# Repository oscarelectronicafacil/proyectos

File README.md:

Este repositorio es para almacenar todos los archivos necesarios para generar los prototipos, los proyectos realizados en las paginas webs OscarElectronicaFacil y hazloconarduino.

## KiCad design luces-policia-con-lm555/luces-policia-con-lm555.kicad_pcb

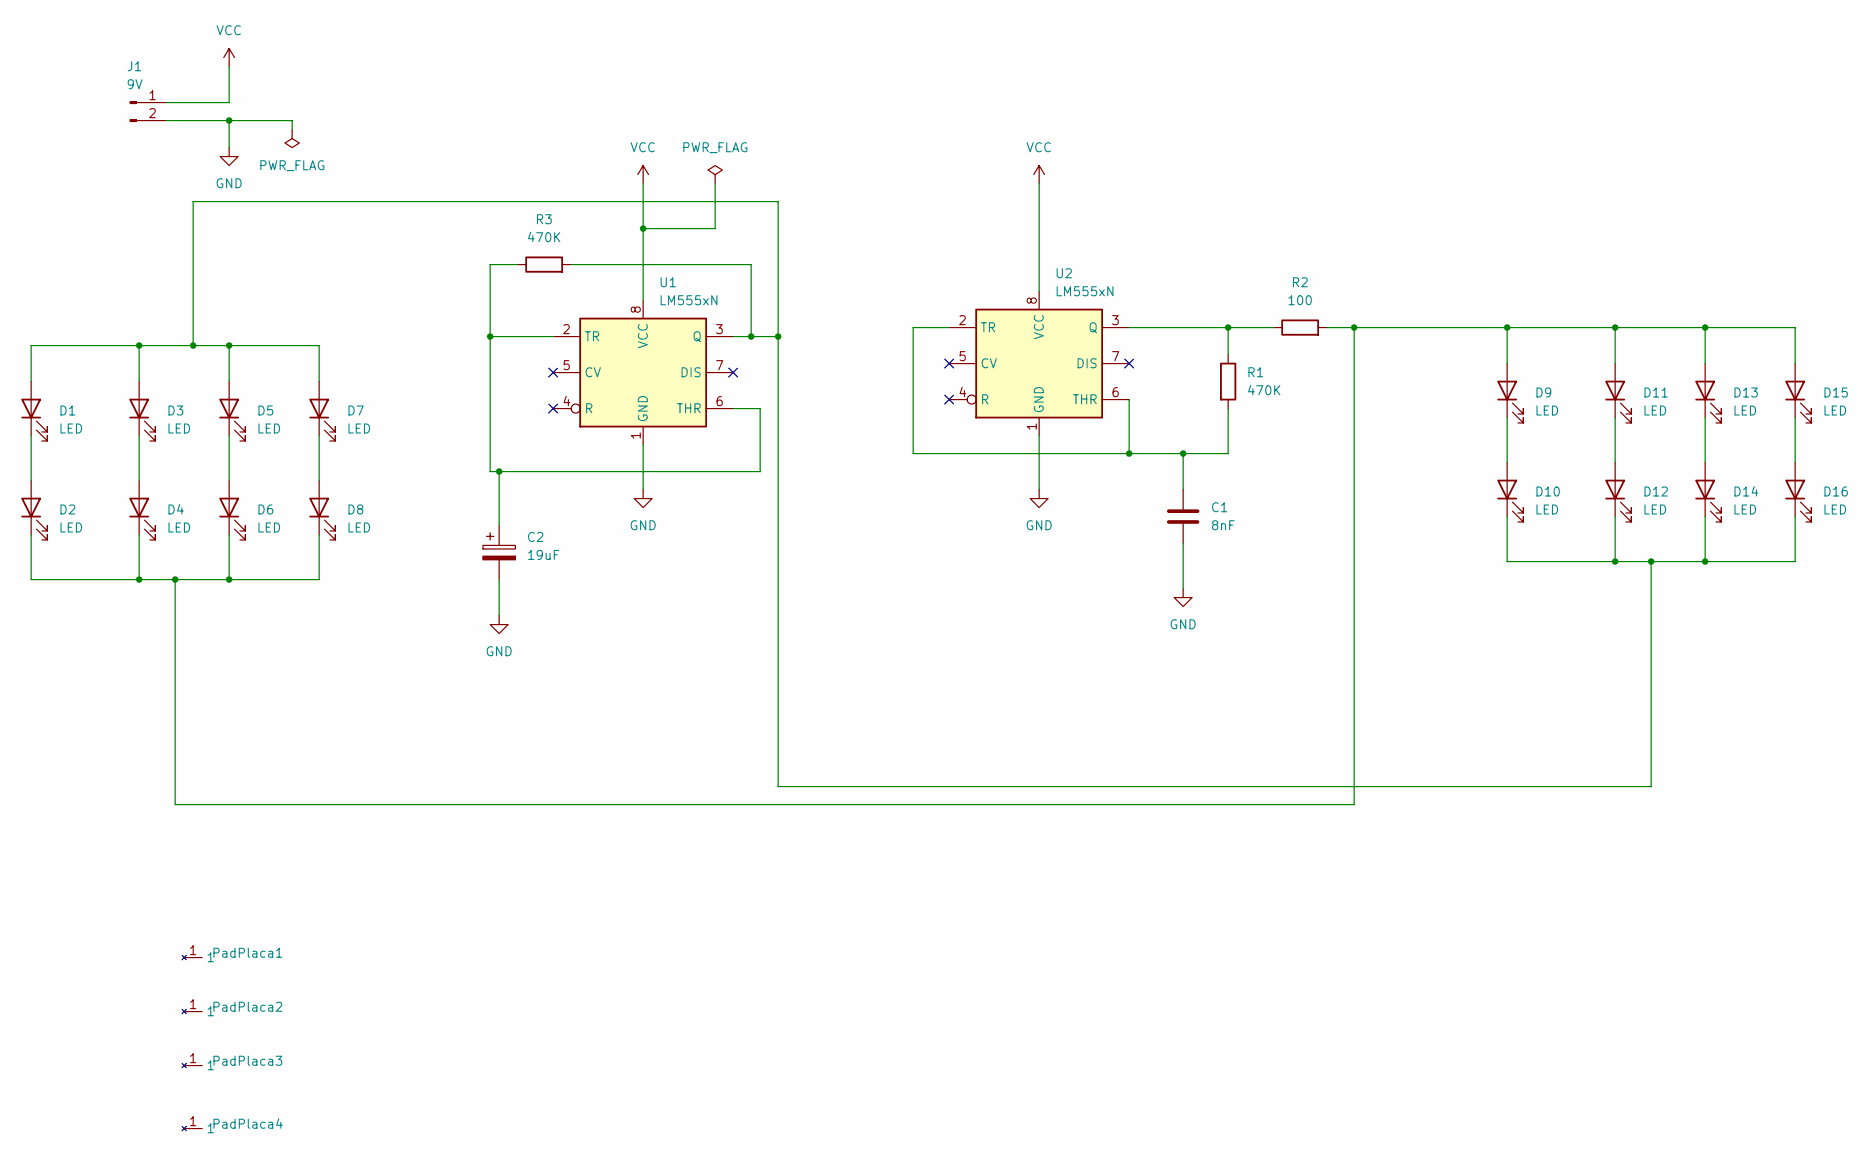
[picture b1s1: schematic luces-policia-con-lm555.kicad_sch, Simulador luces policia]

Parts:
C1: 8nF; C_Axial_L3.8mm_D2.6mm_P7.50mm_Horizontal
C2: 19uF; CP_Radial_D5.0mm_P2.50mm
D1, D2, D3, D4, D5, D6, D7, D8, D9, D10, D11, D12, D13, D14, D15, D16: LED; LED_D5.0mm
J1: 9V; PhoenixContact_MKDS_1,5_2-1727010-1x02_P3.50mm
PadPlaca1, PadPlaca2, PadPlaca3, PadPlaca4: pad
R1, R3: 470K; R_Axial_DIN0207_L6.3mm_D2.5mm_P10.16mm_Horizontal
R2: 100; R_Axial_DIN0207_L6.3mm_D2.5mm_P10.16mm_Horizontal
U1, U2: LM555xN; DIP-8_W7.62mm

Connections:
GND: C1.2, C2.2, J1.2, U1.1 (GND), U2.1 (GND)
unnamed: D1.2 (A), D3.2 (A), D5.2 (A), D7.2 (A), D10.1 (K), D12.1 (K), D14.1 (K), D16.1 (K), R3.2, U1.3 (Q)
unnamed: D1.1 (K), D2.2 (A)
unnamed: D3.1 (K), D4.2 (A)
unnamed: D5.1 (K), D6.2 (A)
unnamed: D7.1 (K), D8.2 (A)
unnamed: D9.1 (K), D10.2 (A)
unnamed: D2.1 (K), D4.1 (K), D6.1 (K), D8.1 (K), D9.2 (A), D11.2 (A), D13.2 (A), D15.2 (A), R2.2
unnamed: D11.1 (K), D12.2 (A)
unnamed: D13.1 (K), D14.2 (A)
unnamed: D15.1 (K), D16.2 (A)
unnamed: C2.1, R3.1, U1.2 (TR), U1.6 (THR)
unnamed: R1.1, R2.1, U2.3 (Q)
unnamed: C1.1, R1.2, U2.2 (TR), U2.6 (THR)
VCC: J1.1, U1.8 (VCC), U2.8 (VCC)

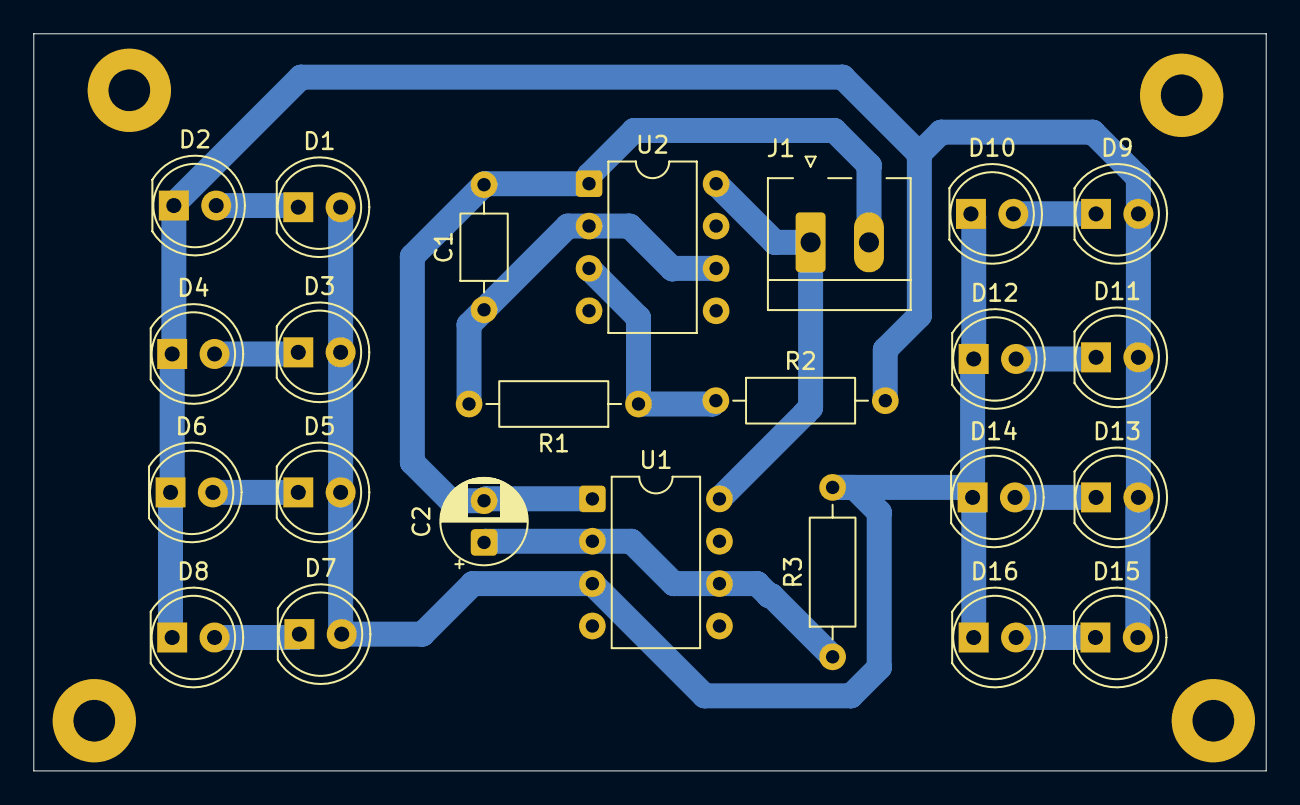
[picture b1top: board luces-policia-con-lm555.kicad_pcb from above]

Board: 2 copper layers, 73.9 x 44.2 mm, 28 parts (0 on the bottom side), 15 nets.

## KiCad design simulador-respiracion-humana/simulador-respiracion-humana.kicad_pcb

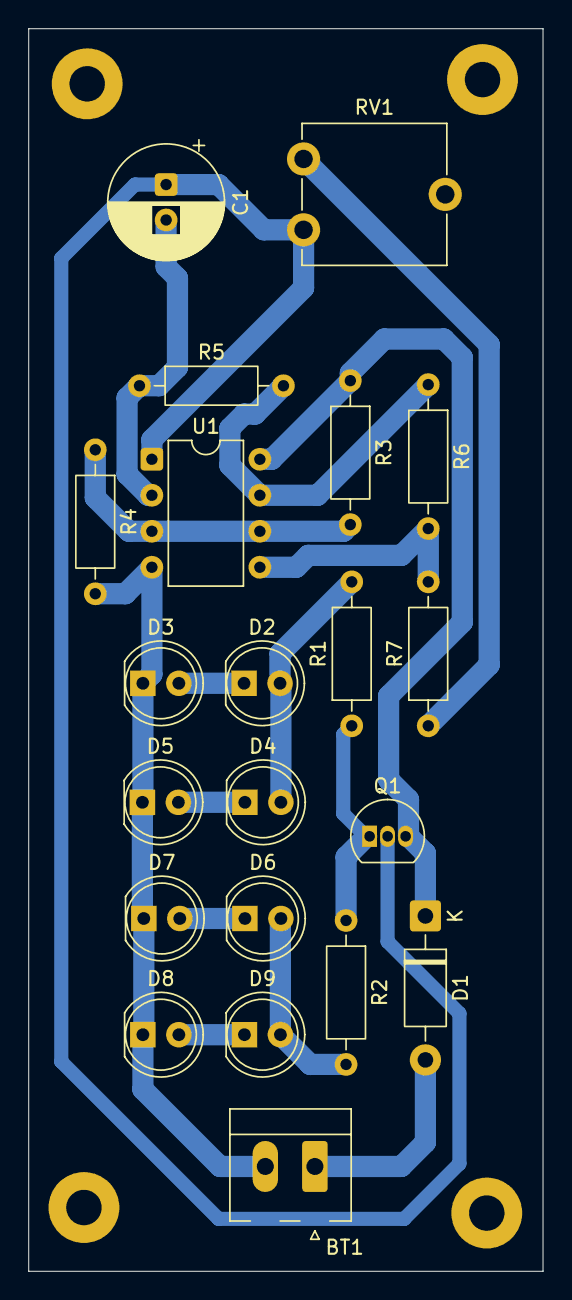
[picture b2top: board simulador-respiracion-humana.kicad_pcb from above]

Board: 2 copper layers, 36.3 x 87.7 mm, 25 parts (0 on the bottom side), 16 nets.

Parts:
BT1: 9V; PhoenixContact_MKDS_1,5_2-1727010-1x02_P3.50mm
C1: 22uF; CP_Radial_D8.0mm_P2.50mm
D1: 1N4007; D_DO-41_SOD81_P10.16mm_Horizontal
D2, D3, D4, D5, D6, D7, D8, D9: LED; LED_D5.0mm
PadPlaca1, PadPlaca2, PadPlaca3, PadPlaca4: pad
Q1: S8050; TO-92_Inline
R1, R2: 100; R_Axial_DIN0207_L6.3mm_D2.5mm_P10.16mm_Horizontal
R3, R4, R5: 47K; R_Axial_DIN0207_L6.3mm_D2.5mm_P10.16mm_Horizontal
R6: 100K; R_Axial_DIN0207_L6.3mm_D2.5mm_P10.16mm_Horizontal
R7: 33K; R_Axial_DIN0207_L6.3mm_D2.5mm_P10.16mm_Horizontal
RV1: 100K; Potentiometer_ACP_CA9-V10_Vertical
U1: DIP-8_W7.62mm

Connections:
unnamed: BT1.1 (+), D1.2 (A)
unnamed: BT1.2 (-), D3.1 (K), D5.1 (K), D7.1 (K), D8.1 (K), R4.2, U1.4
unnamed: C1.2, R5.1, U1.2
unnamed: D1.1 (K), Q1.3 (C), R3.1, U1.8
unnamed: D2.2 (A), D4.2 (A), R1.2
unnamed: D2.1 (K), D3.2 (A)
unnamed: D4.1 (K), D5.2 (A)
unnamed: D6.2 (A), D9.2 (A), R2.2
unnamed: D6.1 (K), D7.2 (A)
unnamed: D8.2 (A), D9.1 (K)
unnamed: C1.1, Q1.2 (B), RV1.1, U1.1
unnamed: Q1.1 (E), R1.1, R2.1
unnamed: R3.2, R4.1, U1.3, U1.6
unnamed: R5.2, R6.1, U1.7
unnamed: R6.2, R7.2, U1.5
unnamed: R7.1, RV1.3

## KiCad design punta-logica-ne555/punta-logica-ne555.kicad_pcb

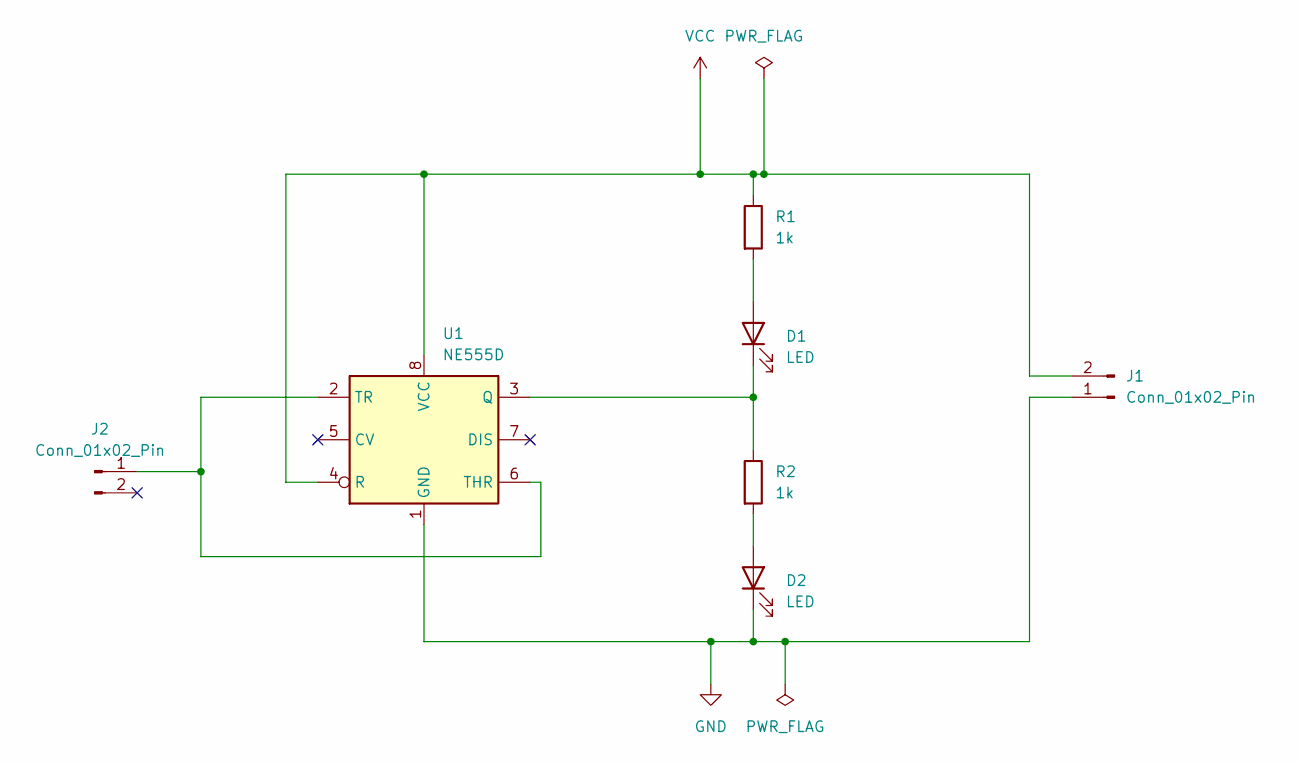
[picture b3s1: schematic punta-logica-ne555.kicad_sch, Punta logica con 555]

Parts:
D1, D2: LED; LED_D5.0mm
J1, J2: Conn_01x02_Pin; PhoenixContact_MKDS_1,5_2-1727010-1x02_P3.50mm
R1, R2: 1k; R_Axial_DIN0207_L6.3mm_D2.5mm_P15.24mm_Horizontal
U1: NE555D; CERDIP-8_W7.62mm_SideBrazed_LongPads_Socket

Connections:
GND: D2.1 (K), J1.1, U1.1 (GND)
unnamed: D1.2 (A), R1.2
unnamed: D1.1 (K), R2.1, U1.3 (Q)
unnamed: D2.2 (A), R2.2
unnamed: J2.1, U1.2 (TR), U1.6 (THR)
VCC: J1.2, R1.1, U1.4 (R), U1.8 (VCC)

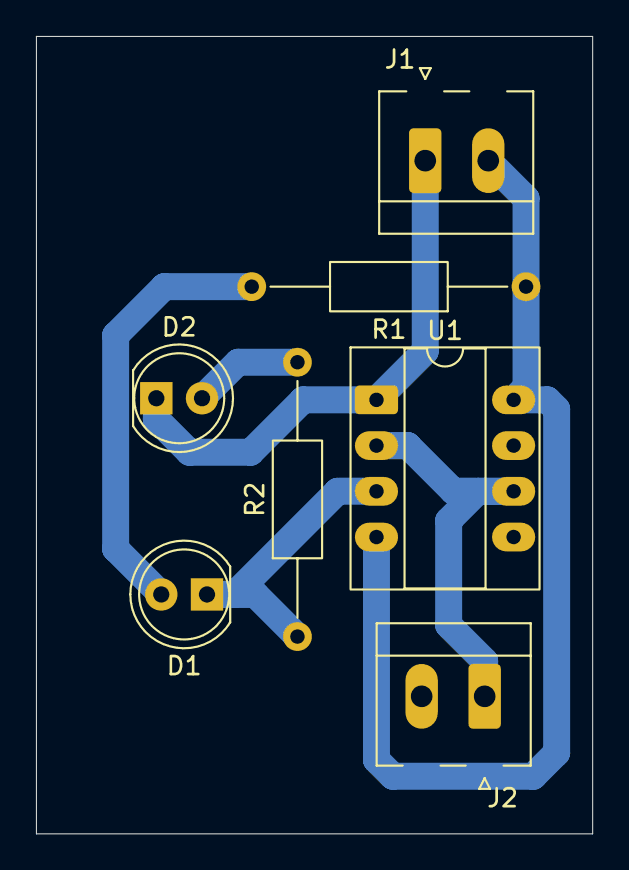
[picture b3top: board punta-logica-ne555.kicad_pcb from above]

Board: 2 copper layers, 30.9 x 44.3 mm, 7 parts (0 on the bottom side), 6 nets.

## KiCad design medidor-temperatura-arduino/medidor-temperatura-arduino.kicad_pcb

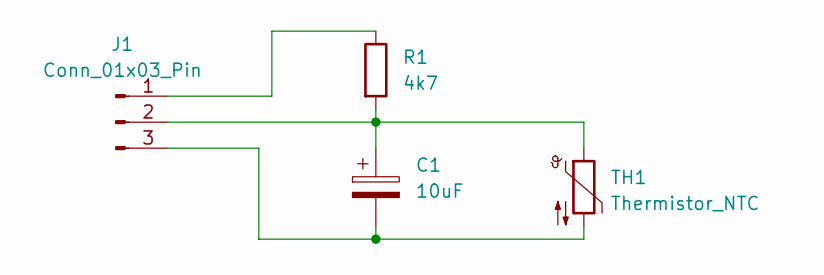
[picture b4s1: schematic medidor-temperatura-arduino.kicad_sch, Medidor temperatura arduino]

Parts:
C1: 10uF; CP_Radial_D6.3mm_P2.50mm
J1: Conn_01x03_Pin; PhoenixContact_MKDS_1,5_3-19325191-1x03_P3.50mm
R1: 4k7; R_Axial_DIN0207_L6.3mm_D2.5mm_P15.24mm_Horizontal
TH1: Thermistor_NTC; PhoenixContact_MKDS_1,5_2-1727010-1x02_P3.50mm

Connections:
unnamed: J1.1, R1.1
unnamed: C1.1, J1.2, R1.2, TH1.1
unnamed: C1.2, J1.3, TH1.2

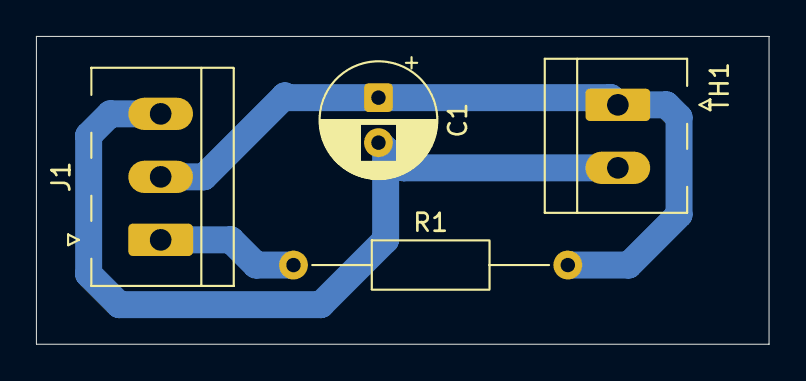
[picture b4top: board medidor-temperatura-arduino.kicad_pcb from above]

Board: 2 copper layers, 40.7 x 17.1 mm, 4 parts (0 on the bottom side), 3 nets.

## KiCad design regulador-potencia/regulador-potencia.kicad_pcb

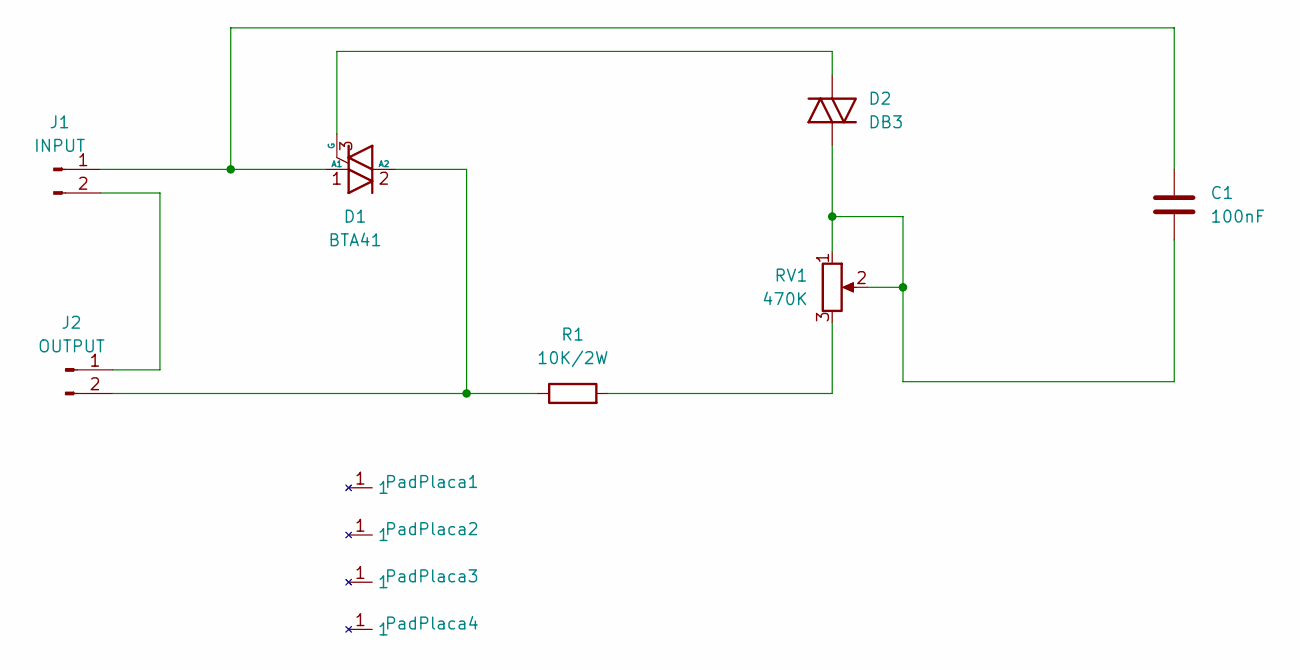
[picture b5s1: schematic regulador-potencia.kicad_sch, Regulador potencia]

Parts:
C1: 100nF; C_Disc_D10.0mm_W2.5mm_P5.00mm
D1: BTA41; TO-3PB-3_Vertical
D2: DB3; D_DO-35_SOD27_P7.62mm_Horizontal
J1: INPUT; PhoenixContact_MKDS_1,5_2-1727010-1x02_P3.50mm
J2: OUTPUT; PhoenixContact_MKDS_1,5_2-1727010-1x02_P3.50mm
PadPlaca1, PadPlaca2, PadPlaca3, PadPlaca4: pad
R1: 10K/2W; R_Axial_DIN0207_L6.3mm_D2.5mm_P15.24mm_Horizontal
RV1: 470K; PhoenixContact_MKDS_1,5_3-19325191-1x03_P3.50mm

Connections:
unnamed: C1.1, D1.1 (A1), J1.1
unnamed: D1.2 (A2), J2.2, R1.1
unnamed: D1.3 (G), D2.2 (A)
unnamed: C1.2, D2.1 (K), RV1.1, RV1.2
unnamed: J1.2, J2.1
unnamed: R1.2, RV1.3

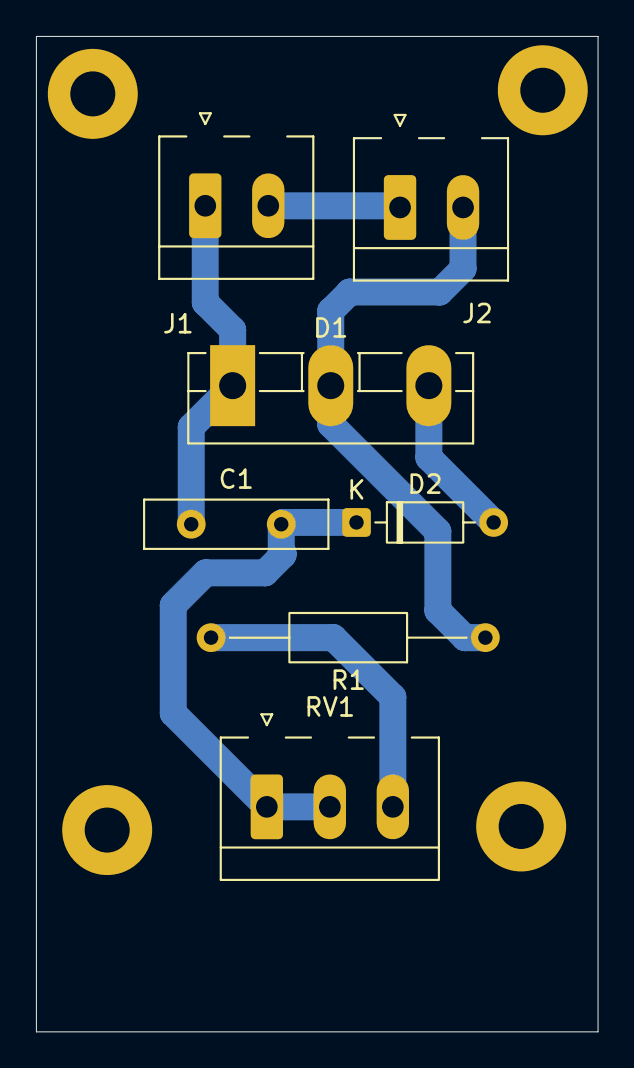
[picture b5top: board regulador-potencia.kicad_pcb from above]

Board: 2 copper layers, 31.2 x 55.3 mm, 11 parts (0 on the bottom side), 6 nets.

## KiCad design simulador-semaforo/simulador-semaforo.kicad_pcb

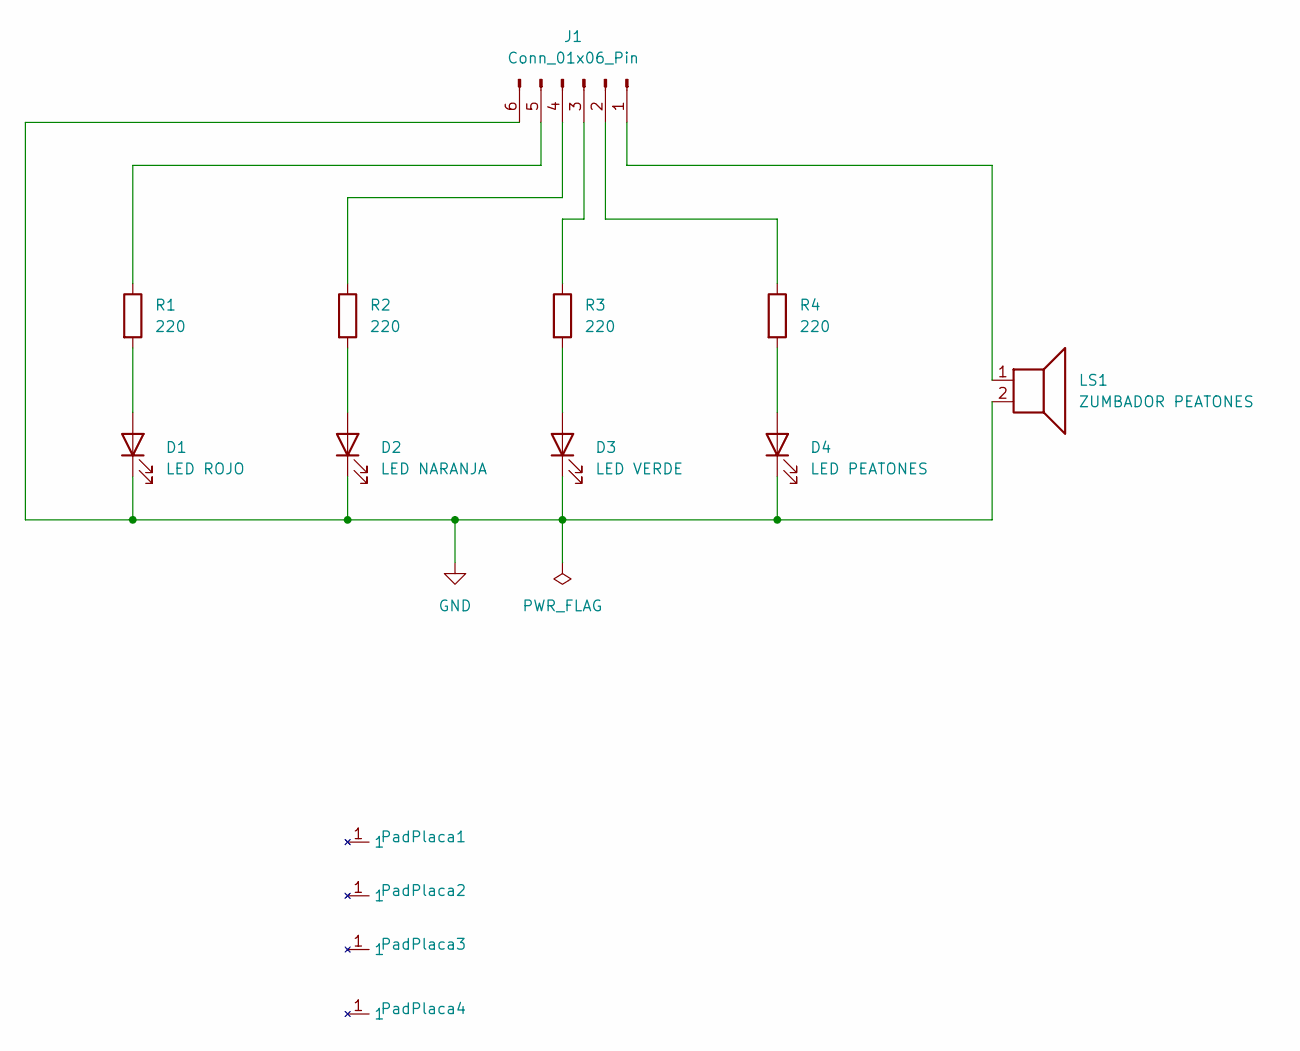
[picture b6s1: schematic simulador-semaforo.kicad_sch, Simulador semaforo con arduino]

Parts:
D1: LED ROJO; LED_D5.0mm
D2: LED NARANJA; LED_D5.0mm
D3: LED VERDE; LED_D5.0mm
D4: LED PEATONES; LED_D5.0mm
J1: Conn_01x06_Pin; PinHeader_1x06_P2.00mm_Vertical
LS1: ZUMBADOR PEATONES; PinHeader_1x02_P2.00mm_Vertical
PadPlaca1, PadPlaca2, PadPlaca3, PadPlaca4: pad
R1, R2, R3, R4: 220; R_Axial_DIN0207_L6.3mm_D2.5mm_P15.24mm_Horizontal

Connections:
GND: D1.1 (K), D2.1 (K), D3.1 (K), D4.1 (K), J1.6, LS1.2
unnamed: D1.2 (A), R1.2
unnamed: D2.2 (A), R2.2
unnamed: D3.2 (A), R3.2
unnamed: D4.2 (A), R4.2
unnamed: J1.1, LS1.1
unnamed: J1.2, R4.1
unnamed: J1.3, R3.1
unnamed: J1.4, R2.1
unnamed: J1.5, R1.1

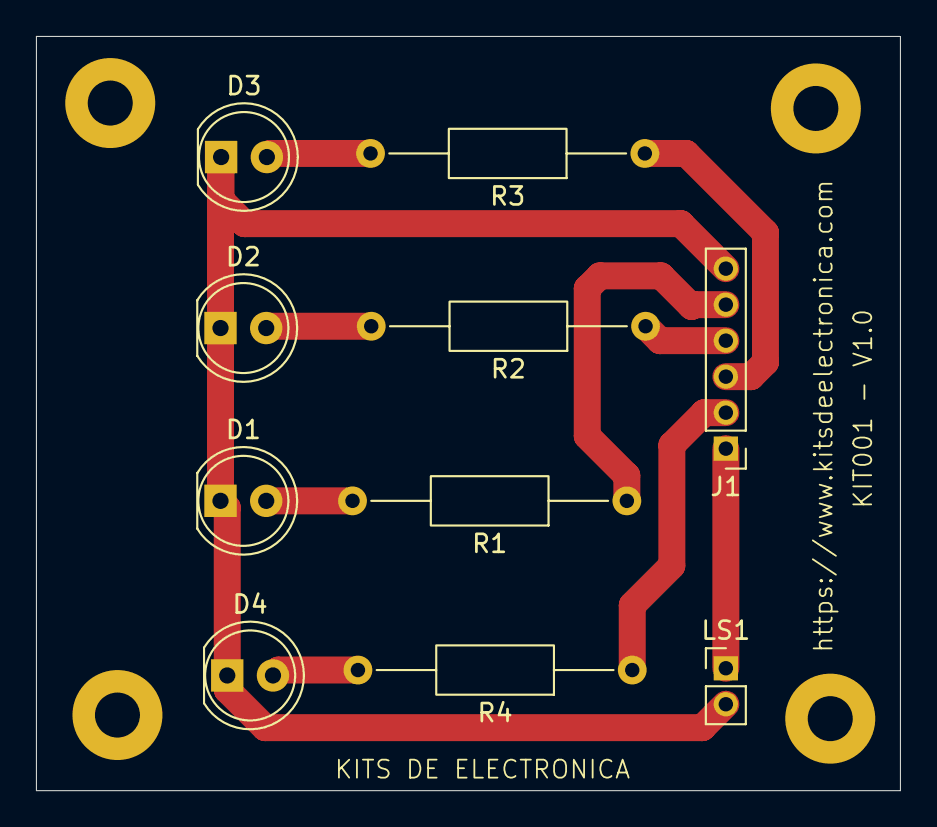
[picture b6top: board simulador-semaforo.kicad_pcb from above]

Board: 2 copper layers, 48.0 x 41.9 mm, 14 parts (0 on the bottom side), 10 nets.

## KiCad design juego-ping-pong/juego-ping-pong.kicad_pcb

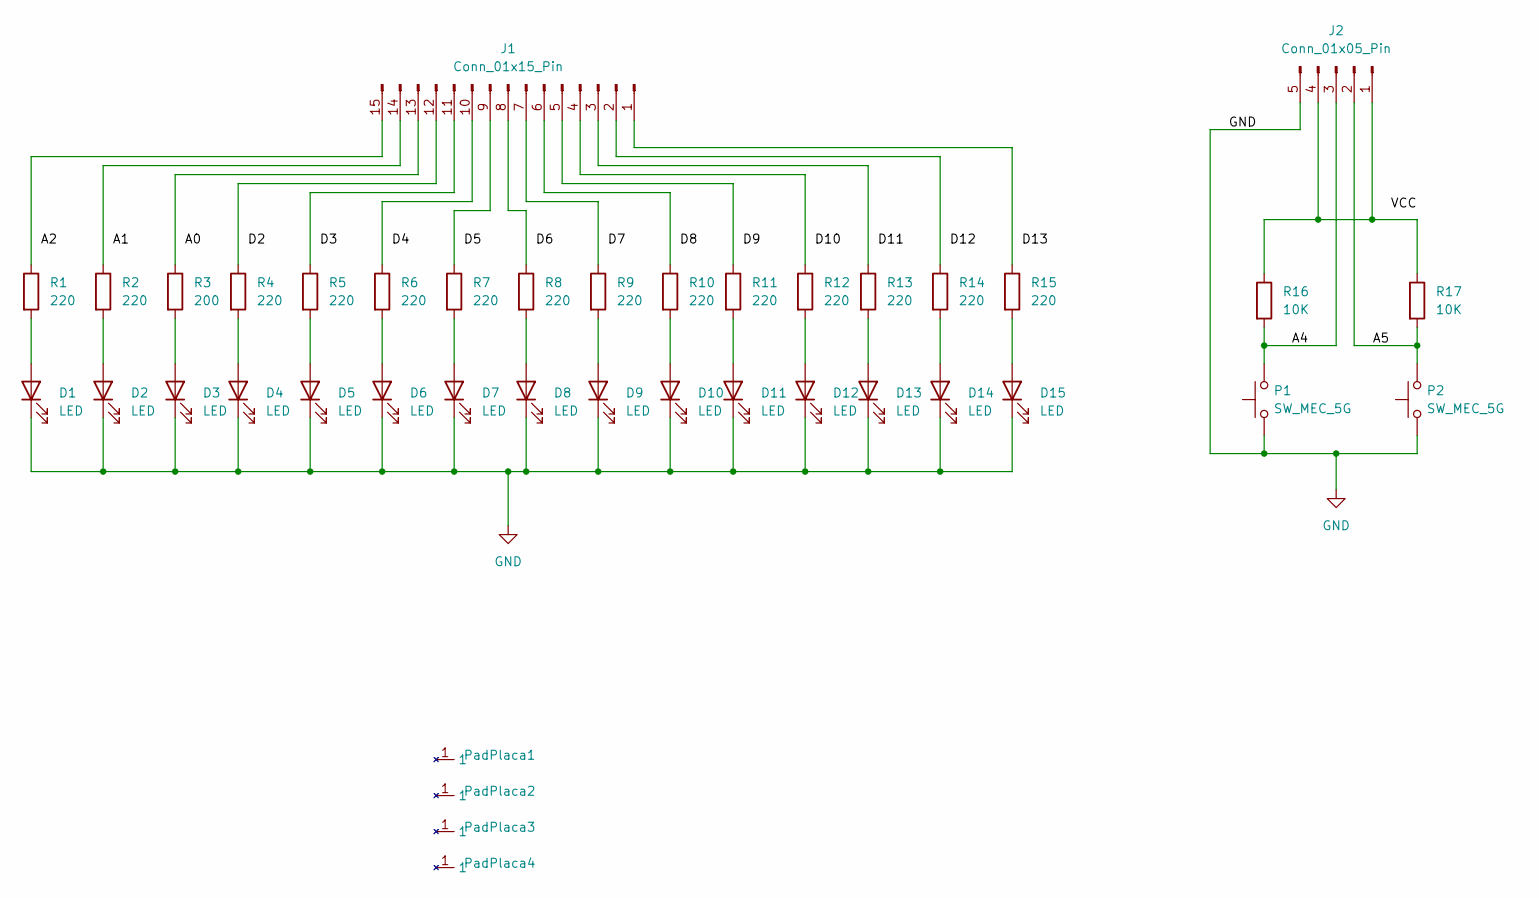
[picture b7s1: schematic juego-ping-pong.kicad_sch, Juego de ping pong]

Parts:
D1, D2, D3, D4, D5, D6, D7, D8, D9, D10, D11, D12, D13, D14, D15: LED; LED_D5.0mm
J1: Conn_01x15_Pin; PhoenixContact_MCV_1,5_15-G-3.5_1x15_P3.50mm_Vertical
J2: Conn_01x05_Pin; PhoenixContact_MCV_1,5_5-G-3.5_1x05_P3.50mm_Vertical
P1, P2: SW_MEC_5G; SW_PUSH_6mm
PadPlaca1, PadPlaca2, PadPlaca3, PadPlaca4: pad
R1, R2, R4, R5, R6, R7, R8, R9, R10, R11, R12, R13, R14, R15: 220; R_Axial_DIN0207_L6.3mm_D2.5mm_P15.24mm_Horizontal
R3: 200; R_Axial_DIN0207_L6.3mm_D2.5mm_P15.24mm_Horizontal
R16, R17: 10K; R_Axial_DIN0207_L6.3mm_D2.5mm_P15.24mm_Horizontal

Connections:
/A4: J2.3, P1.2 (B), R16.2
/A5: J2.2, P2.2 (B), R17.2
GND: D1.1 (K), D2.1 (K), D3.1 (K), D4.1 (K), D5.1 (K), D6.1 (K), D7.1 (K), D8.1 (K), D9.1 (K), D10.1 (K), D11.1 (K), D12.1 (K), D13.1 (K), D14.1 (K), D15.1 (K), J2.5, P1.1 (A), P2.1 (A)
unnamed: D1.2 (A), R1.2
unnamed: D2.2 (A), R2.2
unnamed: D3.2 (A), R3.2
unnamed: D4.2 (A), R4.2
unnamed: D5.2 (A), R5.2
unnamed: D6.2 (A), R6.2
unnamed: D7.2 (A), R7.2
unnamed: D8.2 (A), R8.2
unnamed: D9.2 (A), R9.2
unnamed: D10.2 (A), R10.2
unnamed: D11.2 (A), R11.2
unnamed: D12.2 (A), R12.2
unnamed: D13.2 (A), R13.2
unnamed: D14.2 (A), R14.2
unnamed: D15.2 (A), R15.2
unnamed: J1.1, R15.1
unnamed: J1.2, R14.1
unnamed: J1.3, R13.1
unnamed: J1.4, R12.1
unnamed: J1.5, R11.1
unnamed: J1.6, R10.1
unnamed: J1.7, R9.1
unnamed: J1.8, R8.1
unnamed: J1.9, R7.1
unnamed: J1.10, R6.1
unnamed: J1.11, R5.1
unnamed: J1.12, R4.1
unnamed: J1.13, R3.1
unnamed: J1.14, R2.1
unnamed: J1.15, R1.1
unnamed: J2.1, J2.4, R16.1, R17.1

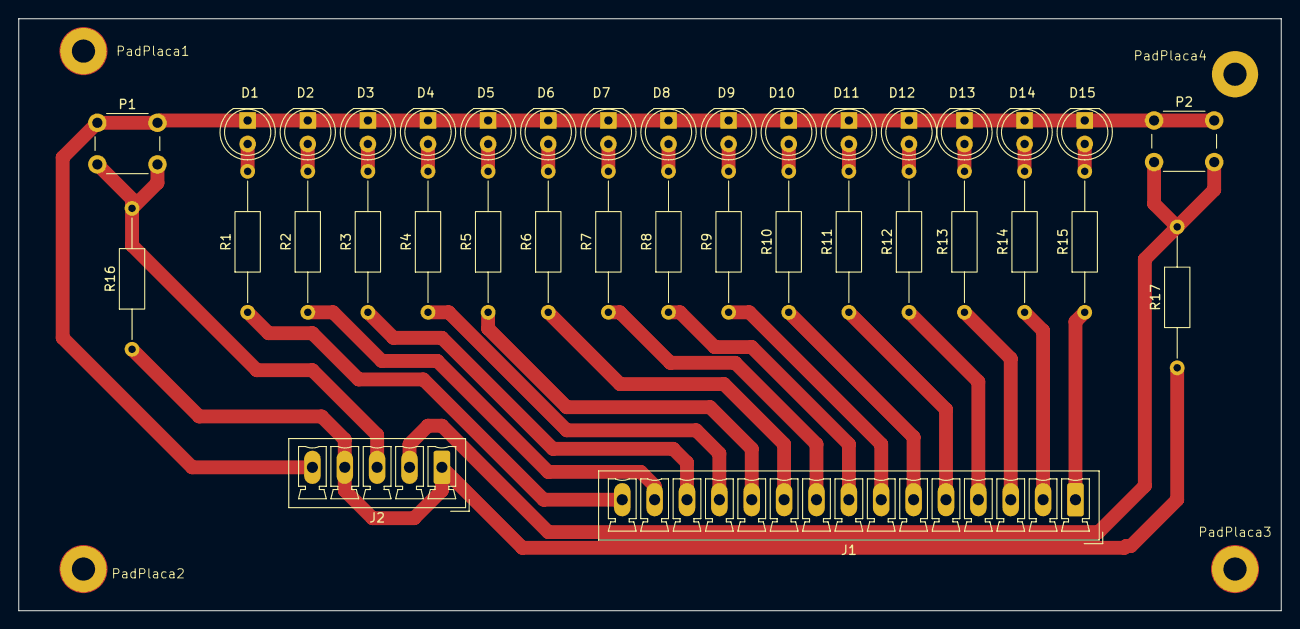
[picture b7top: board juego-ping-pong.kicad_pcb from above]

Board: 2 copper layers, 136.5 x 64.0 mm, 40 parts (0 on the bottom side), 34 nets.

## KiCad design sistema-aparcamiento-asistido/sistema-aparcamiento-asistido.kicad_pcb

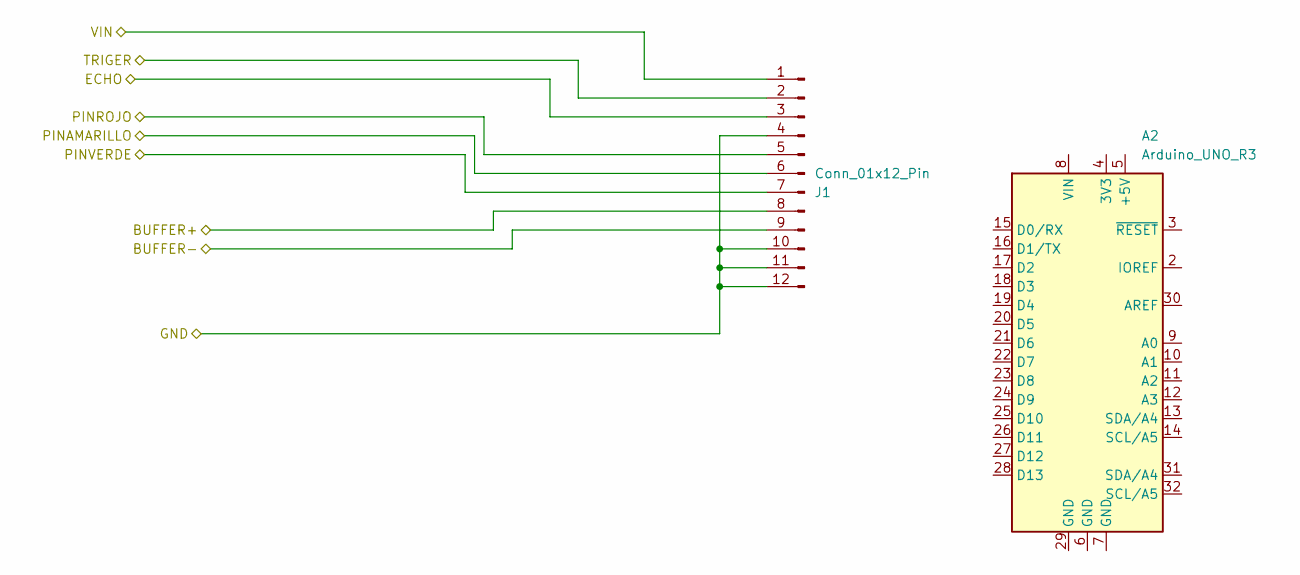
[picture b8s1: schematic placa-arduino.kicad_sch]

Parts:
A2: Arduino_UNO_R3
J1: Conn_01x12_Pin; PhoenixContact_GMSTBVA_2,5_12-G_1x12_P7.50mm_Vertical

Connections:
BUZZER+: J1.8; also elsewhere on the board
BUZZER-: J1.9; also elsewhere on the board
ECHO: J1.3; also elsewhere on the board
GND: J1.4, J1.10, J1.11, J1.12; also elsewhere on the board
PINAMARILLO: J1.6; also elsewhere on the board
PINROJO: J1.5; also elsewhere on the board
PINVERDE: J1.7; also elsewhere on the board
TRIGGER: J1.2; also elsewhere on the board
VCC: J1.1; also elsewhere on the board

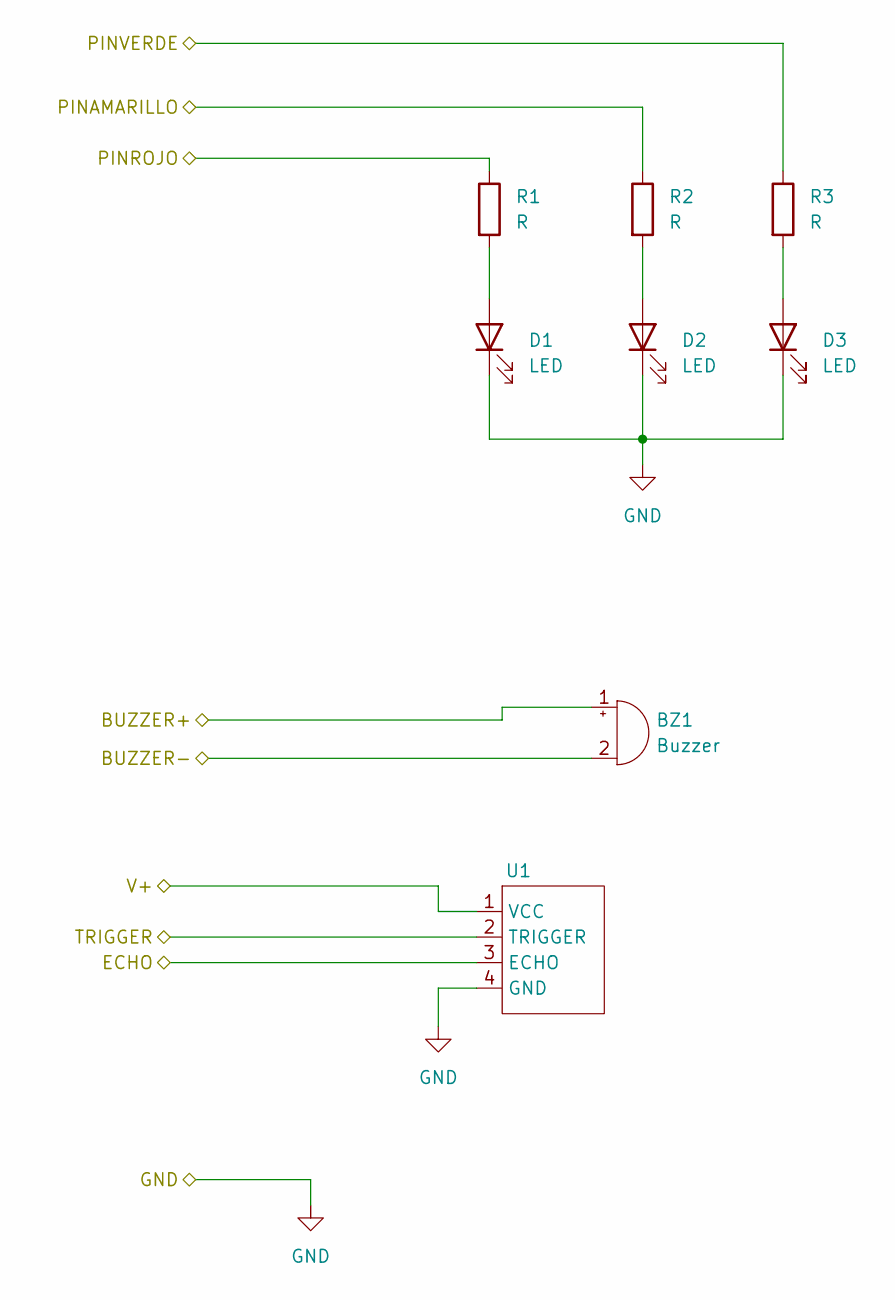
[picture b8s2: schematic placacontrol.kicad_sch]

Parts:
BZ1: Buzzer; Banana_Jack_2Pin
D1, D2, D3: LED; LED_D5.0mm
R1, R2, R3: R; R_Axial_DIN0207_L6.3mm_D2.5mm_P15.24mm_Horizontal
U1: FanPinHeader_1x04_P2.54mm_Vertical

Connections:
BUZZER+: BZ1.1 (+); also elsewhere on the board
BUZZER-: BZ1.2 (-); also elsewhere on the board
ECHO: U1.3 (ECHO); also elsewhere on the board
GND: D1.1 (K), D2.1 (K), D3.1 (K), U1.4 (GND); also elsewhere on the board
unnamed: D1.2 (A), R1.2
unnamed: D2.2 (A), R2.2
unnamed: D3.2 (A), R3.2
PINAMARILLO: R1.1; also elsewhere on the board
PINROJO: R2.1; also elsewhere on the board
PINVERDE: R3.1; also elsewhere on the board
TRIGGER: U1.2 (TRIGGER); also elsewhere on the board
VCC: U1.1 (VCC); also elsewhere on the board

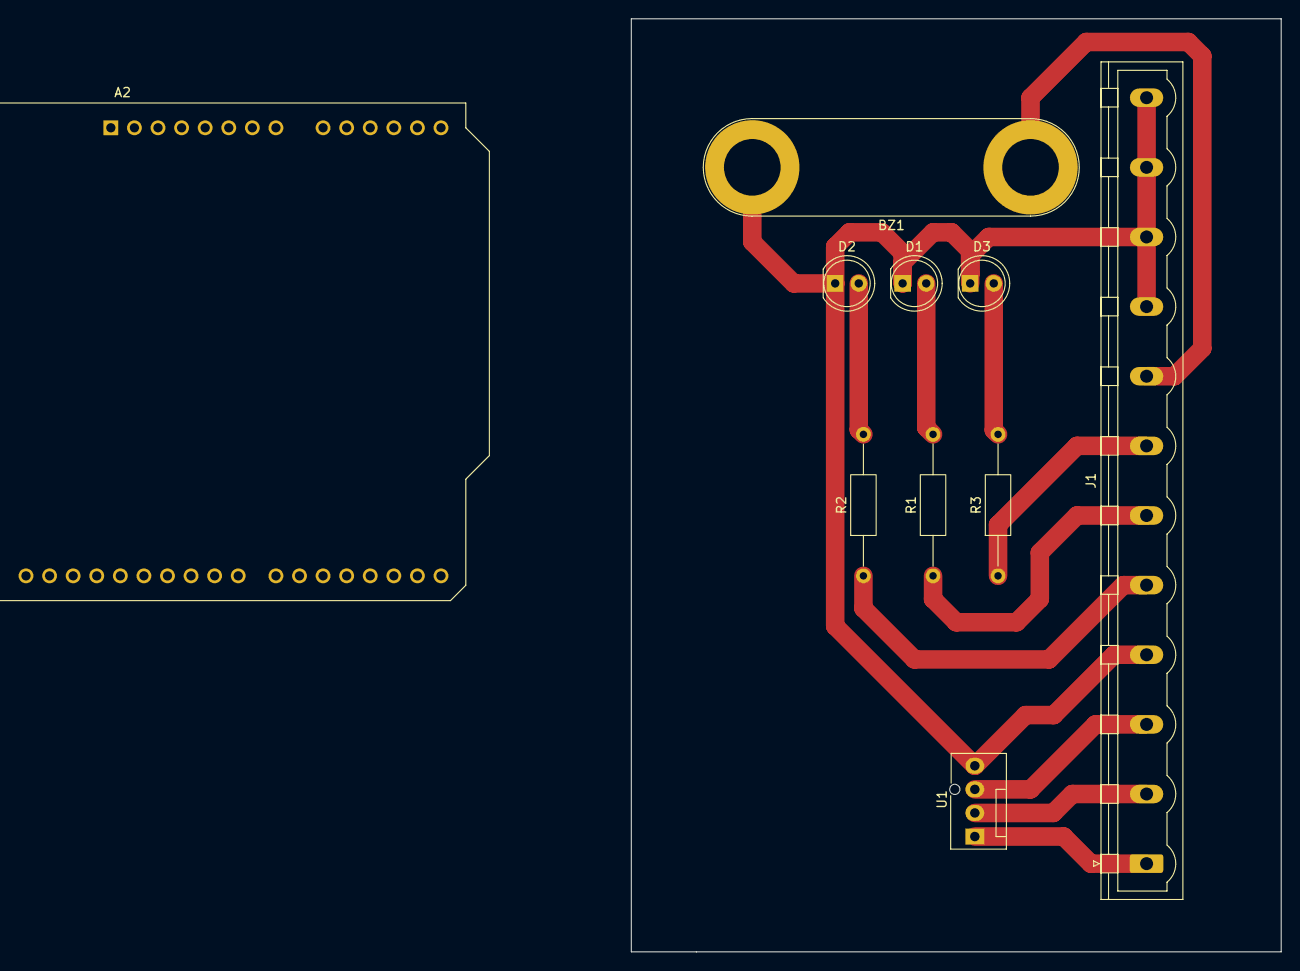
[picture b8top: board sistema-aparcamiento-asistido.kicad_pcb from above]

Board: 2 copper layers, 70.0 x 100.5 mm, 10 parts (0 on the bottom side), 12 nets.
